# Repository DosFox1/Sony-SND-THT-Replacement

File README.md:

# Sony SND THT Replacement 
A replacement for the Sony SND IC (part number 343-0045-A) as used on the Macintosh Plus, SE and others.
This was designed for the Macintosh Plus Clone project, but should be able to be used in other Macintoshes.

**So, What Is It?**

The Sony SND is a custom IC, developed by Sony for the Macintosh Plus. 
It has three main functions - volume control, audio amplification, as well as providing the POR (Power On Reset) signal for the system. 
The original IC represents one of three custom pieces of silicon found with the Macintosh Plus. 

This board replaces the original Sony SND with equivalent circuitry. 
The Power On Reset deisgn is taken from the book _The 68000 microprocessor : hardware and software principles and applications_
This is currently available on the internet archive: https://archive.org/details/68000microproces00jame

Whereas the design for the audio amplification and volume control was taken from the original Macintosh 128/512 schematics:
https://forums.macrumors.com/threads/macintosh-512k-schematic.2291827/

**Parts List**

The SND is comprised of relatively easy to find, off the shelf parts:
```blocks
C1       100n 50V       100N_TH_CAP            CAP_5.08MM_PITCH 1
C2       100n 50V       100N_TH_CAP            CAP_5.08MM_PITCH 1
C3       100n 50V       100N_TH_CAP            CAP_5.08MM_PITCH 1
C4       100n 50V       100N_TH_CAP            CAP_5.08MM_PITCH 1
C5       1u 50V         1U_TH_ELEC_CAPVERTICAL CAP_ELECTROLYTIC 1
C6       100n 50V       100N_TH_CAP            CAP_5.08MM_PITCH 1
C7       470p 50V       470P_TH_CAP            CAP_5.08MM_PITCH 1
C8       1n 50V         1N_TH_CAP              CAP_5.08MM_PITCH 1
C9       100n 50V       100N_TH_CAP            CAP_5.08MM_PITCH 1
C10      100n 50V       100N_TH_CAP            CAP_5.08MM_PITCH 1
C11      220p 50V       220P_TH_CAP            CAP_5.08MM_PITCH 1
D1       5.1V Zener     ZENER-DIODEF126-10     F126Z10          1
IC1      TL072P         TL072P                 DIL08            1
IC2      4016N          4016N                  DIL14            1
IC3      74LS05N        74LS05N                DIL14            1
IC4      555            555P                   DIP08            1
CN1      Header         Turned Pin Header      DIP16 Header     16
Q1       2N3906         2N3906                 TO92             1
Q2       2N3904         2N3904                 TO92D            1
R1       1M             1M_TH_RESISTOR         RESISTORTHRUHOLE 1
R2       1M             1M_TH_RESISTOR         RESISTORTHRUHOLE 1
R3       6k8            6K8_TH_RESISTOR        RESISTORTHRUHOLE 1
R4       47k            47K_TH_RESISTOR        RESISTORTHRUHOLE 1
R5       1k             1K_TH_RESISTOR         RESISTORTHRUHOLE 1
R6       47k            47K_TH_RESISTOR        RESISTORTHRUHOLE 1
R7       68k            68K_TH_RESISTOR        RESISTORTHRUHOLE 1
R8       150k           150K_TH_RESISTOR       RESISTORTHRUHOLE 1
R9       470k           470K_TH_RESISTOR       RESISTORTHRUHOLE 1
R10      470k           470K_TH_RESISTOR       RESISTORTHRUHOLE 1
R11      200k           200K_TH_RESISTOR       RESISTORTHRUHOLE 1
R12      150R           150R_TH_RESISTOR       RESISTORTHRUHOLE 1
R13      10R            10R_TH_RESISTOR        RESISTORTHRUHOLE 1
```

All components are through hole, and are designed to be easily soldered. 
The PCB can be sourced from your favoured fab house, I prefer JLCPCB (sorry PCBWay) - and only cost $4 for five boards. 

**Assembly Notes and Errata**

This design is the initial VDEV1 version of the SND replacement, and has been tested with the Macintosh Plus Clone project.

The design (being through hole) is unlikely to fit into an existing Macintosh chassis, and was designed as a
"first stab" attempt at making a replacement SND. It is anticipated that a secondary improved SMD design will be more suited to this application.

The zener diode at D1 theoretically should be a 1N5231, but any similar 5.1v zener will suffice. 

Assembly should be fairly straight forward for those with some experience with electronic assembly.

Additionally, as the audio section is based off the original Macintosh 128K, -12V is required, which is not provided by the SND header. 
-12V can be tapped directly from the logic board - either from pin 2 (central pin) of the 7905 -5v regulator, pin 8 of the audio/power header
or from pin 5 of the MC3488 line driver. 
I heavily suggest checking with a multimeter before installation - this may damage the SND adapter, the Macintosh board, or both.

The board should be fitted so that the majority of the boards cover the 6522 and Z8530. It may be necessary to add a standard IC socket to raise the board.

Note - VDEV1 boards were assembled and worked first time. Also note that a TL082 can be subsistuted instead of the TL072 if needed.

# Important Assembly Note!
R11 should be a 200K resistor. It is erroneously marked as a 68K on VDEV1 boards. 
This has been fixed in V1.0

# Very Important Note:
Additionally - resistor R21 on the Macintosh Board itself needs to be snipped off, as this is a 47 ohm pull up to 5V on the POR circuit. 
No clue why Sony designed it this way, but it needs to be removed (or replaced with a 1M, and R1 on the Sony SND replacement DNF'd).

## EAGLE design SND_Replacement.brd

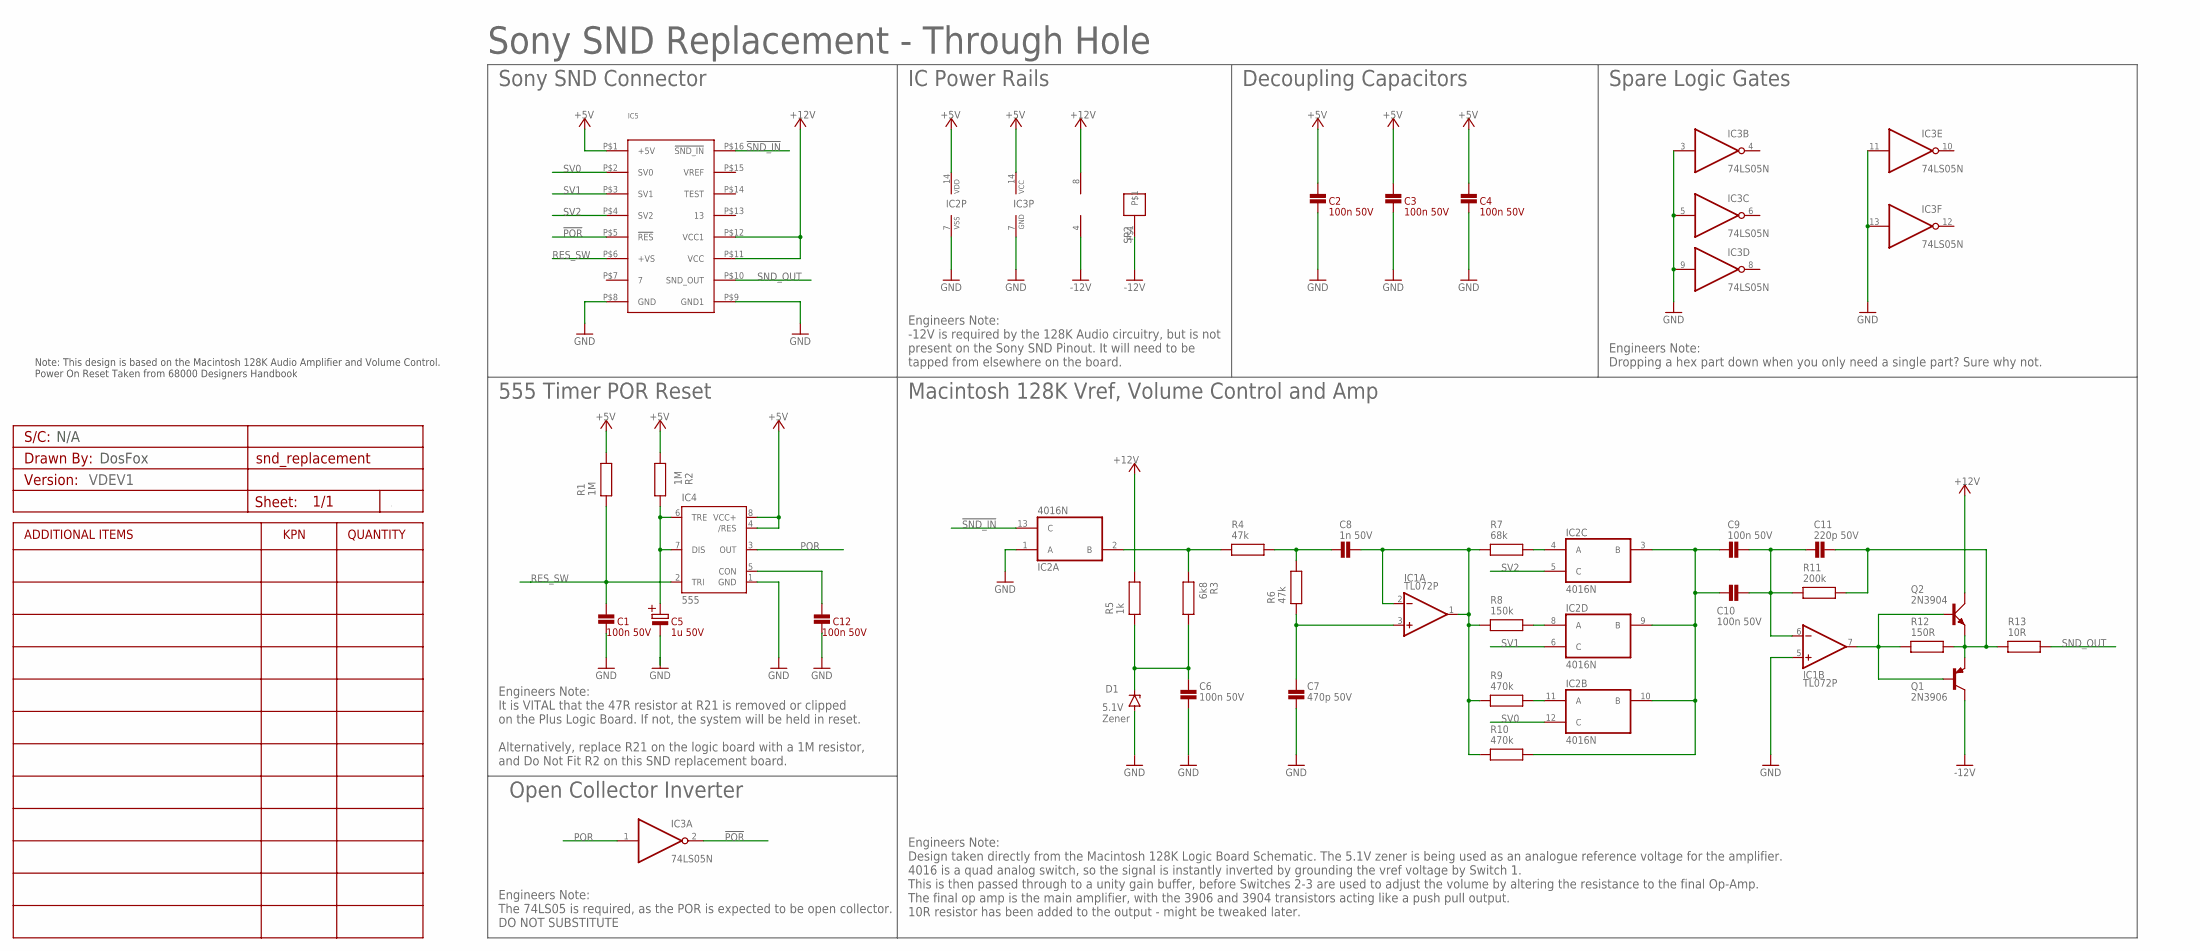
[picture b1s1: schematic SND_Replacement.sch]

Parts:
A1: VDEV1; PCB_CUSTOM_DETAILS
C1, C2, C3, C4, C6, C9, C10, C12: 100n 50V; CAP_5.08MM_PITCH
C5: 1u 50V; CAP_ELECTROLYTIC
C7: 470p 50V; CAP_5.08MM_PITCH
C8: 1n 50V; CAP_5.08MM_PITCH
C11: 220p 50V; CAP_5.08MM_PITCH
D1: ZENER-DIODEF126-10; F126Z10
IC1: TL072P; DIL08
IC2: 4016N; DIL14
IC3: 74LS05N; DIL14
IC4: 555; DIP08
IC5: SND; DIP16
Q1: 2N3906; TO92
Q2: 2N3904; TO92D
R1, R2: 1M; RESISTORTHRUHOLE
R3: 6k8; RESISTORTHRUHOLE
R4, R6: 47k; RESISTORTHRUHOLE
R5: 1k; RESISTORTHRUHOLE
R7: 68k; RESISTORTHRUHOLE
R8: 150k; RESISTORTHRUHOLE
R9, R10: 470k; RESISTORTHRUHOLE
R11: 200k; RESISTORTHRUHOLE
R12: 150R; RESISTORTHRUHOLE
R13: 10R; RESISTORTHRUHOLE
SP2: 1PIN

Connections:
!POR: IC3.2 (O), IC5.P$5 (!RES)
!SND_IN: IC2.13 (C), IC5.P$16 (!SND_IN)
+5V: C2.P$2, C3.P$2, C4.P$2, IC2.14 (VDD), IC3.14 (VCC), IC4.4 (/RES), IC4.8 (VCC+), IC5.P$1 (+5V), R1.P$2, R2.P$2
+12V: IC1.8 (V+), IC5.P$11 (VCC), IC5.P$12 (VCC1), Q2.C, R5.P$2
-12V: IC1.4 (V-), Q1.1 (C), SP2.P$1
GND: C1.P$1, C2.P$1, C3.P$1, C4.P$1, C5.P$2, C6.P$1, C7.P$1, C12.P$1, D1.A, IC1.5 (+IN), IC2.1 (A), IC2.7 (VSS), IC3.3 (I), IC3.5 (I), IC3.7 (GND), IC3.9 (I), IC3.11 (I), IC3.13 (I), IC4.1 (GND), IC5.P$8 (GND), IC5.P$9 (GND1)
unnamed: IC2.2 (B), R3.P$1, R4.P$1
unnamed: C12.P$2, IC4.5 (CON)
unnamed: C9.P$1, C10.P$1, IC2.3 (B), IC2.9 (B), IC2.10 (B), R10.P$2
unnamed: C8.P$1, R4.P$2, R6.P$2
unnamed: C6.P$2, D1.C, R3.P$2, R5.P$1
unnamed: C7.P$2, IC1.3 (+IN), R6.P$1
unnamed: IC2.4 (A), R7.P$2
unnamed: IC2.8 (A), R8.P$2
unnamed: IC2.11 (A), R9.P$2
unnamed: C9.P$2, C10.P$2, C11.P$1, IC1.6 (-IN), R11.P$1
unnamed: C8.P$2, IC1.1 (OUT), IC1.2 (-IN), R7.P$1, R8.P$1, R9.P$1, R10.P$1
unnamed: C11.P$2, Q1.3 (E), Q2.E, R11.P$2, R12.P$2, R13.P$1
unnamed: IC1.7 (OUT), Q1.2 (B), Q2.B, R12.P$1
POR: IC3.1 (I), IC4.3 (OUT)
RES_SW: C1.P$2, IC4.2 (TRI), IC5.P$6 (+VS), R1.P$1
RES_SW1: C5.P$1, IC4.6 (TRE), IC4.7 (DIS), R2.P$1
SND_OUT: IC5.P$10 (SND_OUT), R13.P$2
SV0: IC2.12 (C), IC5.P$2 (SV0)
SV1: IC2.6 (C), IC5.P$3 (SV1)
SV2: IC2.5 (C), IC5.P$4 (SV2)

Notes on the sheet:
Note: This design is based on the Macintosh 128K Audio Amplifier and Volume Control. Power On Reset Taken from 68000 Designers Handbook
DosFox
N/A
5.1V Zener
Sony SND Replacement - Through Hole
Sony SND Connector
IC Power Rails
Decoupling Capacitors
Spare Logic Gates
555 Timer POR Reset
Open Collector Inverter
Macintosh 128K Vref, Volume Control and Amp
Engineers Note: Design taken directly from the Macintosh 128K Logic Board Schematic. The 5.1V zener is being used as an analogue reference voltage for the amplifier. 4016 is a quad analog switch, so the signal is instantly inverted by grounding the vref voltage by Switch 1. This is then passed thro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
Engineers Note: It is VITAL that the 47R resistor at R21 is removed or clipped on the Plus Logic Board. If not, the system will be held in reset. Alternatively, replace R21 on the logic board with a 1M resistor, and Do Not Fit R2 on this SND replacement board.
Engineers Note: The 74LS05 is required, as the POR is expected to be open collector. DO NOT SUBSTITUTE
Engineers Note: -12V is required by the 128K Audio circuitry, but is not present on the Sony SND Pinout. It will need to be tapped from elsewhere on the board.
Engineers Note: Dropping a hex part down when you only need a single part? Sure why not.

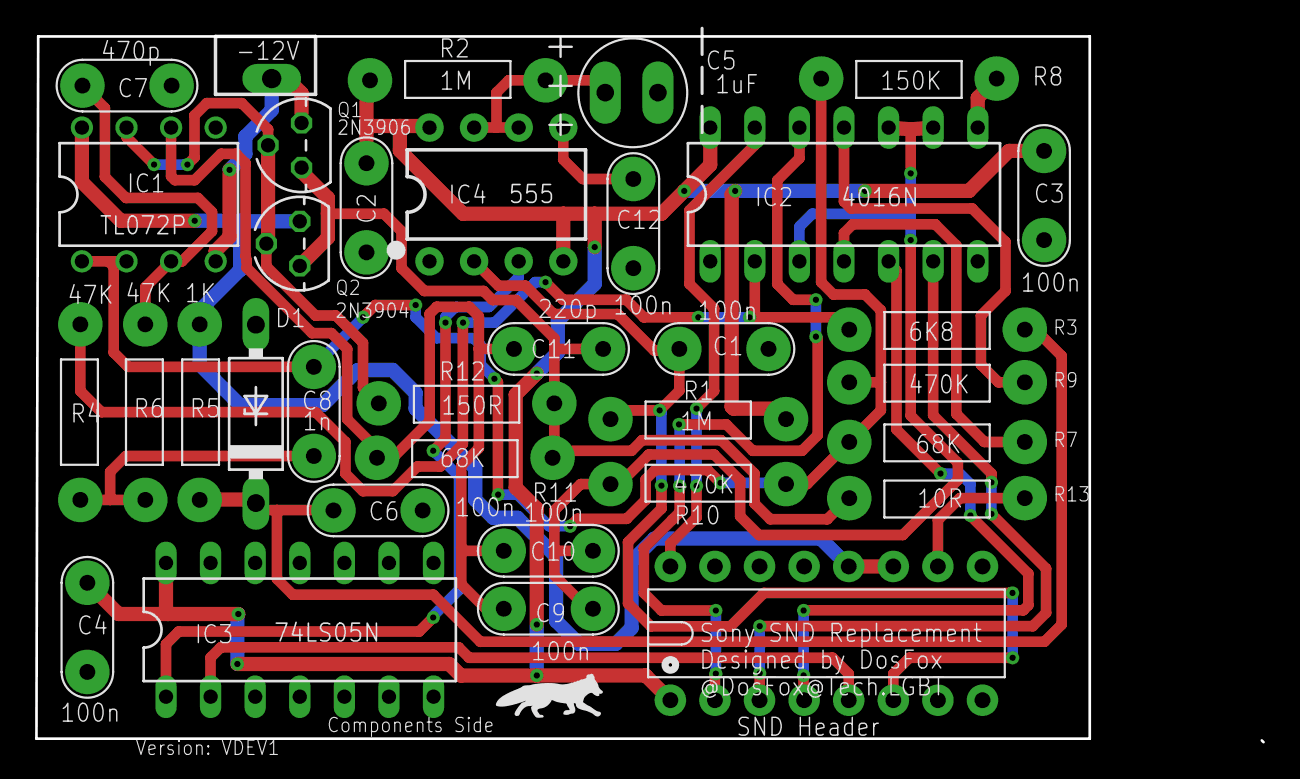
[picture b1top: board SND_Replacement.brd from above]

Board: 2 copper layers, 60.0 x 40.0 mm, 35 parts (0 on the bottom side), 26 nets.

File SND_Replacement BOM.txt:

Partlist

Exported from SND_Replacement.sch at 14/Aug/24 14:49

EAGLE Version 9.6.2 Copyright (c) 1988-2020 Autodesk, Inc.

Assembly variant: 

Part     Value          Device                 Package          Library                      Sheet

C1       100n 50V       100N_TH_CAP            CAP_5.08MM_PITCH Capacitors TH                1
C2       100n 50V       100N_TH_CAP            CAP_5.08MM_PITCH Capacitors TH                1
C3       100n 50V       100N_TH_CAP            CAP_5.08MM_PITCH Capacitors TH                1
C4       100n 50V       100N_TH_CAP            CAP_5.08MM_PITCH Capacitors TH                1
C5       1u 50V         1U_TH_ELEC_CAPVERTICAL CAP_ELECTROLYTIC Capacitors TH                1
C6       100n 50V       100N_TH_CAP            CAP_5.08MM_PITCH Capacitors TH                1
C7       470p 50V       470P_TH_CAP            CAP_5.08MM_PITCH Capacitors TH                1
C8       1n 50V         1N_TH_CAP              CAP_5.08MM_PITCH Capacitors TH                1
C9       100n 50V       100N_TH_CAP            CAP_5.08MM_PITCH Capacitors TH                1
C10      100n 50V       100N_TH_CAP            CAP_5.08MM_PITCH Capacitors TH                1
C11      220p 50V       220P_TH_CAP            CAP_5.08MM_PITCH Capacitors TH                1
D1       5.1V Zener     ZENER-DIODEF126-10     F126Z10          diode                        1
IC1      TL072P         TL072P                 DIL08            linear                       1
IC2      4016N          4016N                  DIL14            40xx                         1
IC3      74LS05N        74LS05N                DIL14            74xx-eu                      1
IC4      555            555P                   DIP08            SparkFun-IC-Special-Function 1
CN1      Header         SND                    DIP16 Header     Header                       1
IC6      74LS05N        74LS05N                DIL14            74xx-eu                      1
Q1       2N3906         2N3906                 TO92             transistor-pnp               1
Q2       2N3904         2N3904                 TO92D            transistor-small-signal      1
R1       1M             1M_TH_RESISTOR         RESISTORTHRUHOLE Resistors TH                 1
R2       1M             1M_TH_RESISTOR         RESISTORTHRUHOLE Resistors TH                 1
R3       6k8            6K8_TH_RESISTOR        RESISTORTHRUHOLE Resistors TH                 1
R4       47k            47K_TH_RESISTOR        RESISTORTHRUHOLE Resistors TH                 1
R5       1k             1K_TH_RESISTOR         RESISTORTHRUHOLE Resistors TH                 1
R6       47k            47K_TH_RESISTOR        RESISTORTHRUHOLE Resistors TH                 1
R7       68k            68K_TH_RESISTOR        RESISTORTHRUHOLE Resistors TH                 1
R8       150k           150K_TH_RESISTOR       RESISTORTHRUHOLE Resistors TH                 1
R9       470k           470K_TH_RESISTOR       RESISTORTHRUHOLE Resistors TH                 1
R10      470k           470K_TH_RESISTOR       RESISTORTHRUHOLE Resistors TH                 1
R11      200k           100K_TH_RESISTOR       RESISTORTHRUHOLE Resistors TH                 1
R12      150R           150K_TH_RESISTOR       RESISTORTHRUHOLE Resistors TH                 1
R13      10R            10R_TH_RESISTOR        RESISTORTHRUHOLE Resistors TH                 1
SP2      1PIN           1PIN                   1PIN             generic parts                1

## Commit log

2024-08-19 Initial README.md
2024-10-15 Add files via upload
    Resolved issue regarding R11 (200K rather than original 68K
2024-10-15 Rename SND_Replacement.pdf to SND_Replacement Schematic.pdf
2024-10-15 Rename SND_Replacement_V1.0.zip to SND_Replacement_V1.0 Gerbers.zip
2024-10-15 Rename Macintosh 128K Logic Board Schematic.pdf to Schematics/Macintosh 128K Logic Board Schematic.pdf
2024-10-15 Rename Macintosh Plus Logic Board Schematic.pdf to Schematics/Macintosh Plus Logic Board Schematic.pdf
2024-10-15 Rename SND_Replacement Schematic.pdf to Schematics/SND_Replacement Schematic.pdf
2024-10-15 Rename SND_Replacement BOM.txt to BOM/SND_Replacement BOM.txt
2024-10-15 Rename SND_Replacement.brd to Eagle/SND_Replacement.brd
2024-10-15 Rename SND_Replacement.sch to Eagle/SND_Replacement.sch
2024-10-15 Rename SND_Replacement_V1.0 Gerbers.zip to Gerbers/SND_Replacement_V1.0 Gerbers.zip
2024-10-15 Rename SND_Replacement_VDEV1_Gerbers.zip to Gerbers/SND_Replacement_VDEV1_Gerbers.zip
2024-10-15 Rename Sony SND Replacement Back.png to Images/Sony SND Replacement Back.png
2024-10-15 Rename Sony SND Replacement Bare PCB.png to Images/Sony SND Replacement Bare PCB.png
2024-10-15 Rename Sony SND Replacement Front.png to Images/Sony SND Replacement Front.png
2024-10-21 Create LICENSE

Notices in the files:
parts and their libraries:
SparkFun-IC-Special-Function: Licensing: Creative Commons ShareAlike 4.0 International - https://creativecommons.org/licenses/by-sa/4.0
